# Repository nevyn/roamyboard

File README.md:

# roamyboard, aka Pants Keyboard

A keyboard you wear on your legs, so you can type while you walk. Each half is a row of 3D-printed modules on a strap: key modules that click together at an angle, so the half curves around a thigh, an MCU module with a nice!nano, a battery and a display, and a terminator module at the far end. It runs ZMK over Bluetooth, and the right half's display has a built-in PDA.

**Photos, the build and more: [roamyboard.nevyn.dev](https://roamyboard.nevyn.dev).** There you'll find the [assembly guide](https://roamyboard.nevyn.dev/assembly/), the [layout](https://roamyboard.nevyn.dev/layout/), the [PDA manual](https://roamyboard.nevyn.dev/pda/), and a page to [order one](https://roamyboard.nevyn.dev/order/).

But why‽ Because I think so much better when I'm moving. So I want to code while I move. So I need an input method that works while I'm moving. The original idea was to literally sew it into pants, but that's too impractical; now it's a strap you put on top of your pants.

I will also need a wearable [computer](roamykit/Computer.md) and [head mounted display](roamykit/Head%20mounted%20display.md) to go with this setup, but that's for later.

Made by [Nevyn Bengtsson](mailto:hello@nevyn.dev) 2012-2026 (this is not the first iteration 😅).

## What's in here

This repo is also an Obsidian vault, which is why it has wiki syntax here and there.

- `case/`: the case. `case/roamy-v4` is the current model, in Cadova (Swift): `swift run` there writes the printable 3MF files. Notes in [Case design](case/Case%20design.md) and [Harness design](case/Harness%20design.md). `roamy-v3.py` is the old CadQuery model.
- `electronics/`: the KiCad project for the key module board, and [Electronics](electronics/Electronics.md) with the bus and the joint.
- `zmk/`: the firmware, ZMK plus a driver for the key modules' shift register chain. [Firmware](docs/firmware.md) covers building, flashing over USB, updating over Bluetooth with `roamy-ota` or a phone, and [Logging](docs/logging.md) reading both halves' logs over Bluetooth with `roamy-log`; [Layout](zmk/Layout.md) covers the keymap.
- `docs/`: the website at roamyboard.nevyn.dev and the reference docs; [docs/index.md](docs/index.md) lists them.
- [Build Diary](Build%20Diary.md): what happened when.
- `firmware/`: the stock Lily58 firmware images from before the roamyboard had its own.

## Inspiration

The construction started from [ScottoChoczard](https://scottokeebs.com/blogs/keyboards/scottochoczard-handwired-keyboard), a hand-wired, PCB-less split that doesn't have to be flat, and the layout from the [Lily58](https://typeractive.xyz/pages/build/lily58), which is wireless on a nice!nano with a conventional four-row layout. Since then it got its own PCBs and modules. More in [Inspiration](Inspiration.md).

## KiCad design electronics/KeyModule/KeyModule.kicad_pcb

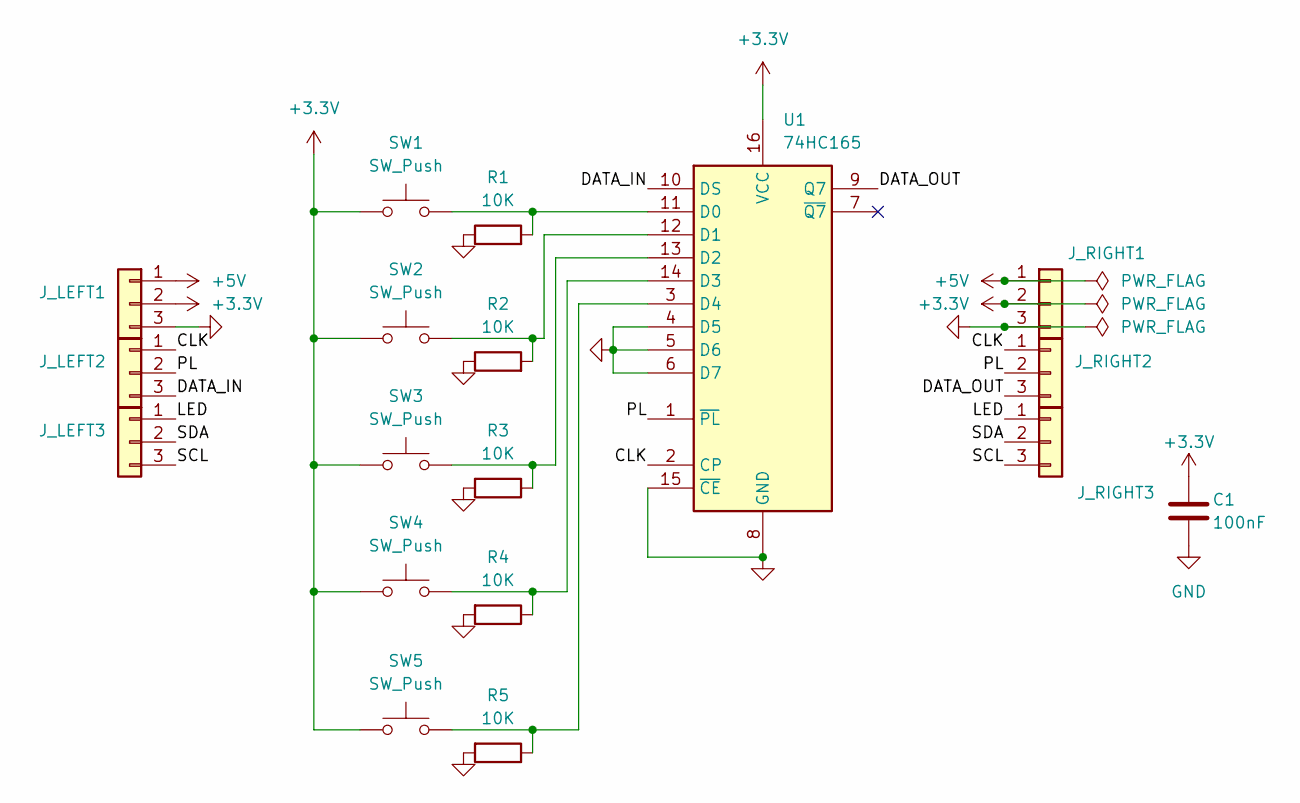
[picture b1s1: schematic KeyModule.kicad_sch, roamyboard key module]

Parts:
C1: 100nF; C_0805_2012Metric; LCSC Part # C49678
J_LEFT1, J_LEFT2, J_LEFT3: HX PM2.54-1x3P WT; Harwin_M20-791_1x03_Horizontal_SMD; LCSC Part # C46061767
J_RIGHT1, J_RIGHT2, J_RIGHT3: HX PZ2.54-1x3P WT; Harwin_M20-889_1x03_Horizontal_SMD; LCSC Part # C46061676
R1, R2, R3, R4, R5: 10K; R_0805_2012Metric; LCSC Part # C17414
SW1, SW2, SW3, SW4, SW5: SW_Push; Kailh_choc_v1_hotswap
U1: 74HC165; SOIC-16_3.9x9.9mm_P1.27mm; LCSC Part # C5613

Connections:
+3.3V: C1.1, J_LEFT1.2, J_RIGHT1.2, SW1.1, SW2.1, SW3.1, SW4.1, SW5.1, U1.16 (VCC)
+5V: J_LEFT1.1, J_RIGHT1.1
/CLK: J_LEFT2.1, J_RIGHT2.1, U1.2 (CP)
/DATA_IN: J_LEFT2.3, U1.10 (DS)
/DATA_OUT: J_RIGHT2.3, U1.9 (Q7)
/LED: J_LEFT3.1, J_RIGHT3.1
/PL: J_LEFT2.2, J_RIGHT2.2, U1.1 (~PL)
/SCL: J_LEFT3.3, J_RIGHT3.3
/SDA: J_LEFT3.2, J_RIGHT3.2
GND: C1.2, J_LEFT1.3, J_RIGHT1.3, R1.1, R2.1, R3.2, R4.2, R5.2, U1.4 (D5), U1.5 (D6), U1.6 (D7), U1.8 (GND), U1.15 (~CE)
unnamed: R1.2, SW1.2, U1.11 (D0)
unnamed: R2.2, SW2.2, U1.12 (D1)
unnamed: R3.1, SW3.2, U1.13 (D2)
unnamed: R4.1, SW4.2, U1.14 (D3)
unnamed: R5.1, SW5.2, U1.3 (D4)

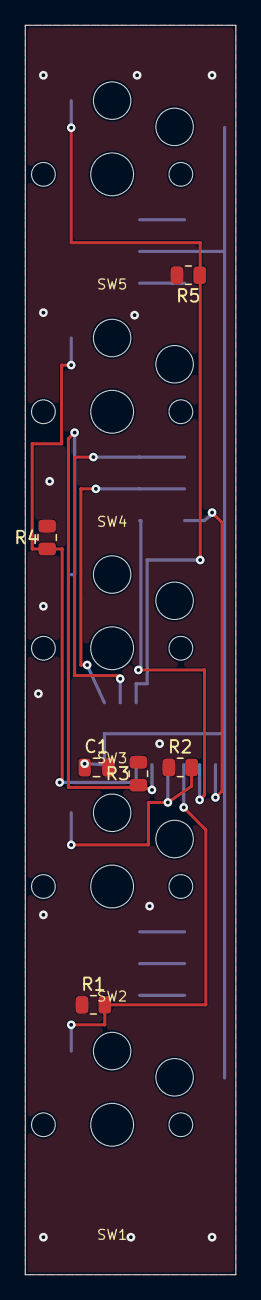
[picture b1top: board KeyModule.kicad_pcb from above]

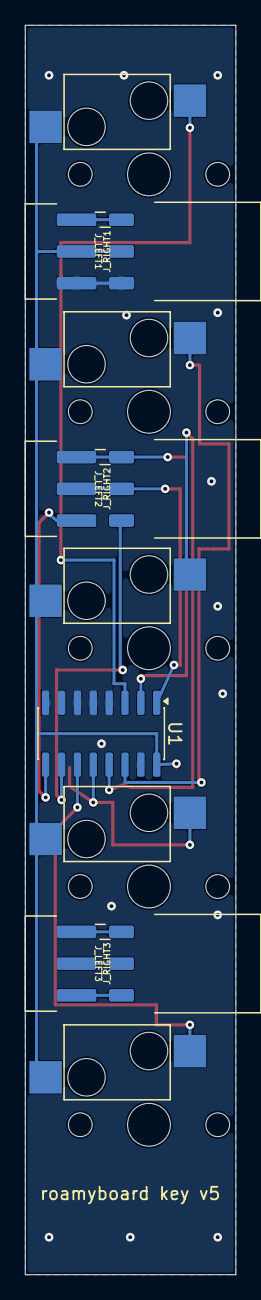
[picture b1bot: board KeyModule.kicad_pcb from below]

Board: 2 copper layers, 16.9 x 100.0 mm, 18 parts (7 on the bottom side), 15 nets.

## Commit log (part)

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2025-02-06 Some initial concept documentation for roamyboard
2025-02-06 some case notes
2025-02-19 Document the creation of Version 1
2025-12-27 docs
2025-12-27 V3 design draft
2025-12-30 WIP case in cadquery
2025-12-30 document case
2026-01-02 Work on 3.1
2026-01-02 I like this clearance algorithm better
2026-01-02 docs, and less wide
2026-01-02 okay, curvature is happening!
2026-01-02 cleanup
2026-01-02 Split for easier printing
2026-01-02 add exporters to the cq script
2026-01-04 Try less clearance for 3.4
2026-01-04 More 3.3 learnings
2026-01-04 3.4: wider modules so keys latch
2026-01-04 3.4: even less clearance, but not quite that much width
2026-01-04 3.4: Screw holes for top plate
2026-01-04 Add stopper to joining groove
2026-01-04 Locking mechanism at top of groove
2026-01-04 document 3.4, and 3.5: create centerline and adjust locking mechanism
2026-01-04 interconnect cutout
2026-01-04 ooh centerline offset is just half prism displacement!
2026-01-04 Bump clearance again
2026-01-04 3.5: re-add space behind locking mechanism, and give it a longer spring
2026-01-04 3.5: Thicker edge walls so we can have m2 screws go through them
2026-01-04 Add clearance for the interconnect so it doesn't collide with the edge wall
2026-01-04 Remove ridges under top plate
2026-01-04 Document 3.5 print learnings
2026-01-04 3.6 WIP modularize and MCU module
2026-01-04 Fix exports
2026-01-04 Recursive subassemblies so they can be disabled. Also fix some constraints and make the MCU module wider
2026-01-04 add nice nano step file
2026-01-04 Let's do 5 rows, not 6
2026-01-05 Remove right socket on MCU module
2026-01-05 cutout and fasteners for mcu
2026-01-05 Screw holes in lid shouldn't attach to lid
2026-01-05 show additional modules
2026-01-05 Try this alternative clearance
2026-01-05 Fix preview key module alignment. why does this happen??
2026-01-05 oops forgot image
2026-01-05 Add clearance to stopper
2026-01-05 preview of 3.6 in docu
2026-01-05 Move MCU further into module so it doesn't break through a too thin wall
2026-01-05 note about pin order
2026-01-06 Prep for 3.7
2026-01-06 3.7: Terminator module
2026-02-02 I did something
2026-02-02 Future plans maybe
2026-02-02 how to run
2026-02-02 Add the harness fasteners to the MCU
2026-02-02 Don't show the expensive previews
2026-02-02 Add fasteners to the terminator as well
2026-02-02 Try to improve the clearance and dimensions of the connecting geometry
2026-02-02 Try to get the battery to fit
2026-02-02 Try to get the MCU to fit too
2026-02-03 Document 3.7, begin 3.8
2026-02-03 Image of 3.6 irl too
2026-02-03 3.8: Longer tongue
2026-02-03 3.8: Less clearance for battery
2026-02-03 3.8: Less clearance for mcu
2026-02-03 I understand that it's technically impossible to see a difference in any change smaller than 0.2mm, but that still won't stop me from trying...
2026-02-04 3.8: Images
2026-02-12 Rename some confusing variables
2026-04-06 Electronics docs start
2026-04-06 Wiring bullets
2026-04-06 Fixup schematic
2026-04-08 KiCad schematics for key module!!!!
2026-04-09 kicad: Make ERC pass
2026-04-09 kicad: footprints
2026-04-10 fixup readme
2026-04-14 kicad something
2026-04-14 electronics documentation
2026-04-14 Build diary
2026-04-14 with dates
2026-04-14 Footprints: SMD so we can do double sided PCB
2026-04-14 Rough layout
2026-04-16 pcm docs, first routing attempt
2026-04-20 wip redo the pcb design with raj
2026-04-20 wip document stuff
